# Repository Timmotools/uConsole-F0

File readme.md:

uConsole to Flipper Zero module adapter PCB files. 

This is the first PCB I have designed in 20 years.

Recently I purchased the uConsole and thought, Wouldnt it be nice to have GPS, CC1101, NRF as modules rather than trying to manually install these. So here we are.

Rev 0.1 board doesnt have a revision number on the board and was the intial design I got made by PCBway. I made and ordered these before I had the uConsole in my hands. The boards I ordered were too thick so it allowed a second revision to be made to fix a few things.
Rev 0.1 only has basic parts. no speaker pads included.

Rev 0.2 will have the speaker pads. The USB holes will be relocated and the Flipper Zero plug will be flipped as I feel its upside down on Rev 0.2

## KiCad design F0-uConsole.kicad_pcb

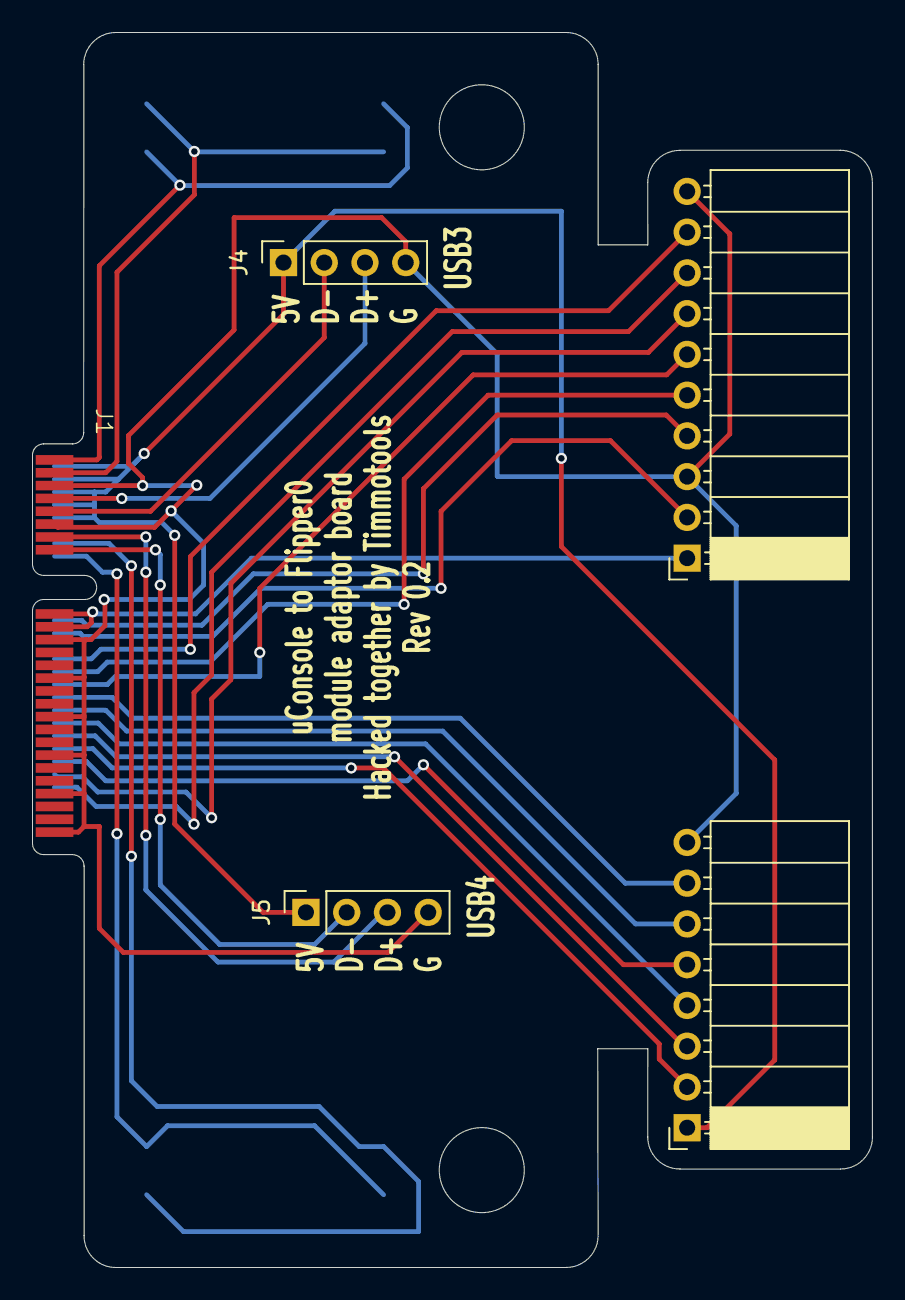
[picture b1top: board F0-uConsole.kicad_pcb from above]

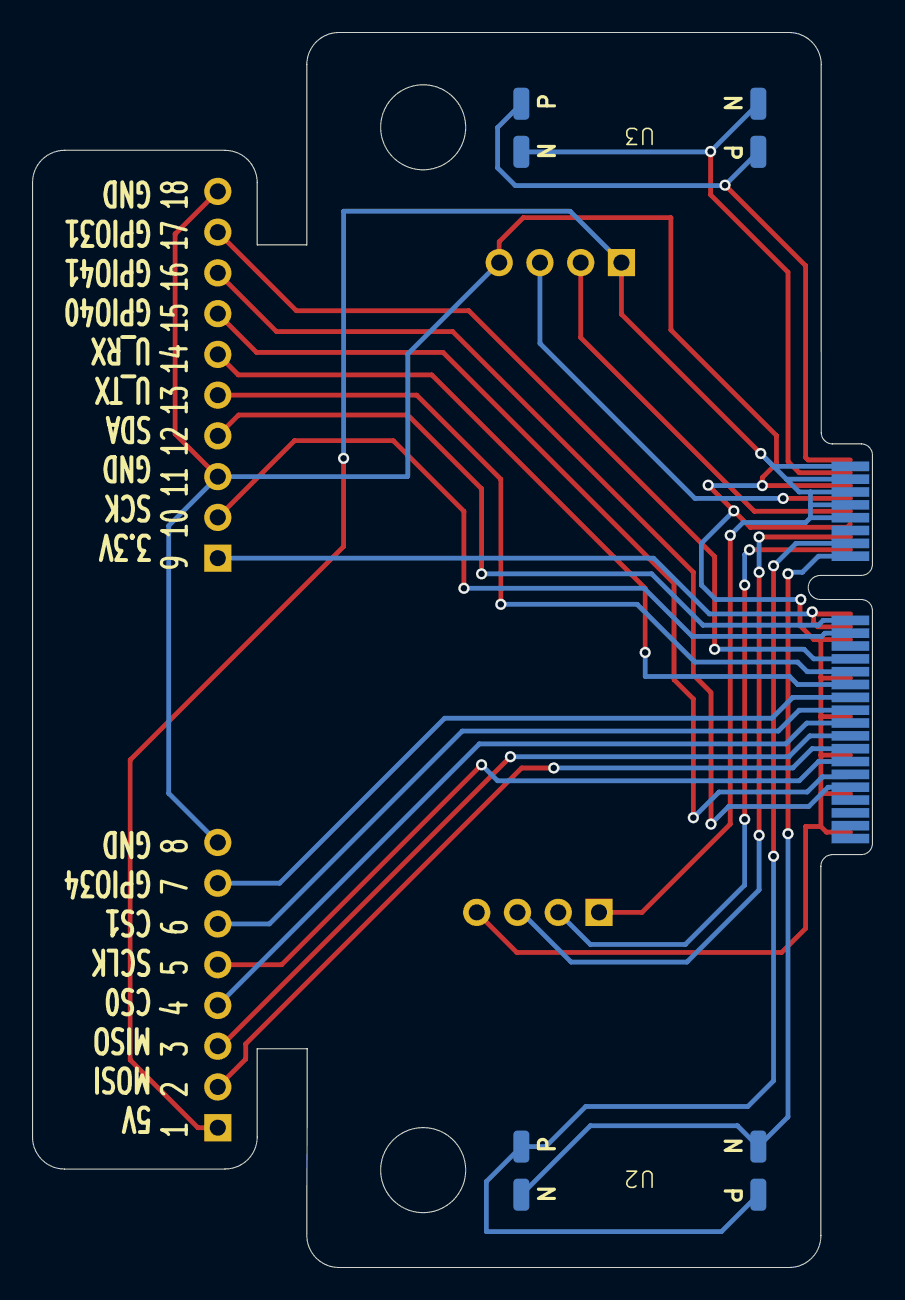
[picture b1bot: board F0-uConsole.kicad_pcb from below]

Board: 2 copper layers, 52.4 x 77.0 mm, 9 parts (2 on the bottom side), 24 nets.

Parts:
H1, H2: MountingHole; MountingHole_5.3mm_M5
J1: uConsoleEXT; ext_connector
J2: F0_1; PinSocket_1x08_P2.54mm_Horizontal
J3: F0_2; PinSocket_1x10_P2.54mm_Horizontal
J4: USB1; PinSocket_1x04_P2.54mm_Vertical
J5: USB2; PinSocket_1x04_P2.54mm_Vertical
U2, U3: Speaker; speaker pads

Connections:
+3.3V: J1.17 (3V3), J1.19 (3V3), J3.1
+5V: J1.2 (5V), J1.4 (5V), J1.6 (5V), J1.8 (5V), J1.10 (5V), J2.1, J4.1, J5.1
/SPK_LN: J1.3 (SPK_LN), U3.2 (N1), U3.4 (N2)
/SPK_LP: J1.1 (SPK_LP), U3.1, U3.3 (P2)
/SPK_RN: J1.16 (SPK_RN), U2.2 (N1), U2.4 (N2)
/SPK_RP: J1.14 (SPK_RP), U2.1, U2.3 (P2)
GND: J1.5 (GND), J1.11 (GND), J1.12 (GND), J1.21 (GND), J1.27 (GND), J1.33 (GND), J1.39 (GND), J1.45 (GND), J1.51 (GND), J2.8, J3.3, J3.10, J4.4, J5.4
GPIO34: J1.30 (GPIO34), J2.7
GPIO40: J1.42 (GPIO40), J3.7
GPIO41: J1.44 (GPIO41), J3.8
RTS0: J1.24 (GPIO31), J3.9
RXD0: J1.28 (GPIO33), J3.6
SCL: J1.20 (GPIO29), J3.2
SDA: J1.18 (GPIO28), J3.4
SPI_CE0: J1.34 (GPIO36), J2.4
SPI_CE1: J1.32 (GPIO35), J2.6
SPI_MISO: J1.36 (GPIO37), J2.3
SPI_MOSI: J1.38 (GPIO38), J2.2
SPI_SCLK: J1.40 (GPIO39), J2.5
TXD0: J1.26 (GPIO32), J3.5
USB3_DN: J1.9 (USB3_DM), J4.2
USB3_DP: J1.7 (USB3_DP), J4.3
USB4_DN: J1.15 (USB4_DM), J5.2
USB4_DP: J1.13 (USB4_DP), J5.3

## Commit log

2025-06-23 upload of Rev 0.1 board.
2025-06-23 add images of Rev 0.1 board
2025-06-25 Upload Rev0.2 board
    change notes:
    added speaker terminals
    flipped the flipper connector so the module face would be facing the user. basically this meant a full redesign.
    shortened the card slightly.
2025-06-25 upload Rev0.2
    forgot the revision on the silkscreen.
